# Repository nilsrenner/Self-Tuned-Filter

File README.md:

# Self-Tuned Filter
Backup für die Bachlorarbeit

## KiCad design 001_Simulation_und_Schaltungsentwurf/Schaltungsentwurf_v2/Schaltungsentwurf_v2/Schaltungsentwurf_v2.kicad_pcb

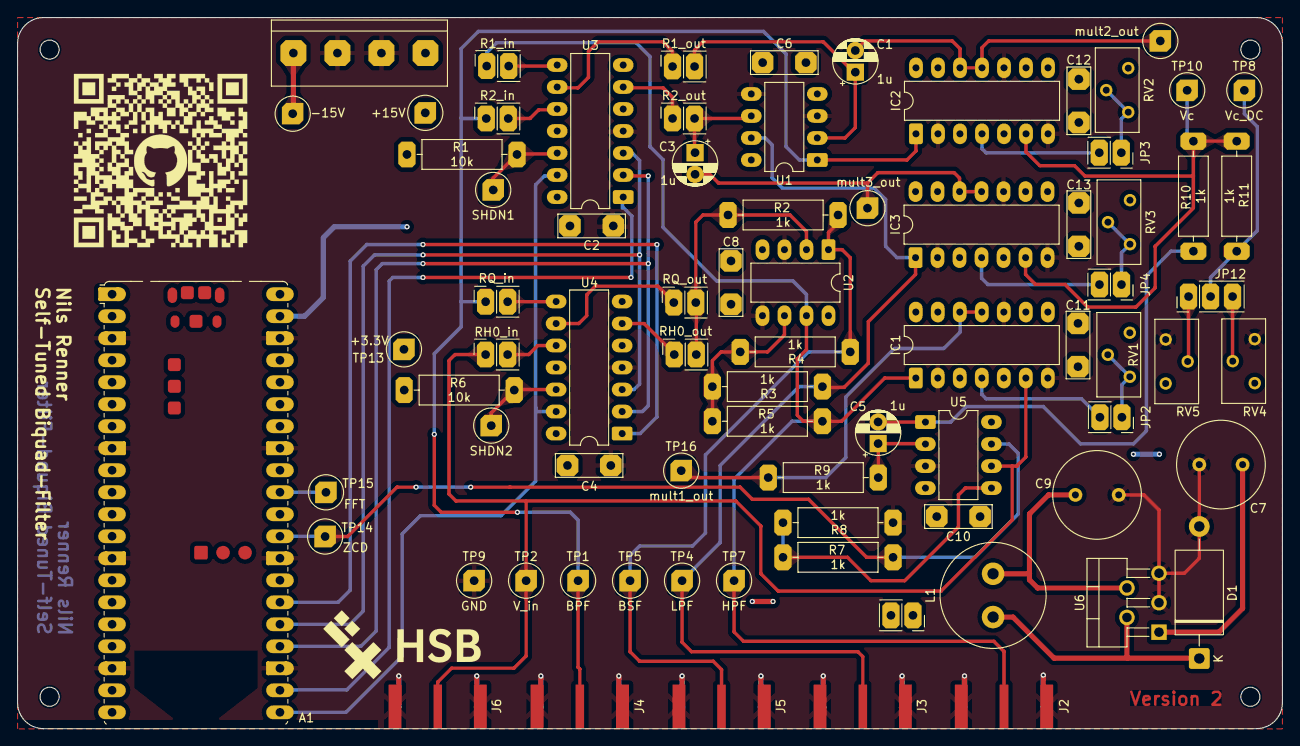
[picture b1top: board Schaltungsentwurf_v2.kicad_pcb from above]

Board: 4 copper layers, 146.0 x 82.1 mm, 84 parts (1 on the bottom side), 48 nets.

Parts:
A1: RaspberryPi_Pico_W; RaspberryPi_Pico_W_THT
C1, C3, C5: 1u; 1-10uF
C2, C4, C6, C8, C10, C11, C12, C13: 100n; 100nF
C7: 470uF; C_Radial_D10.0mm_H16.0mm_P5.00mm
C9: 330uF; C_Radial_D10.0mm_H16.0mm_P5.00mm
D1: 1N5820; D_DO-27_P15.24mm_Horizontal
H1, H2, H3, H4: MountingHole; MountingHole_2.2mm_M2_DIN965
IC1, IC2, IC3: MPY634KP; DIP_14
J1: Screw_Terminal_01x04; Terminal 4 Pol
J2, J3, J4, J5, J6: Conn_Coaxial; BNC Edge Mount
JP1: R1_in; Connector 2 Pin 2.54mm
JP2, JP3, JP4, JP13: Connector 2 Pin 2.54mm
JP5: R1_out; Connector 2 Pin 2.54mm
JP6: R2_in; Connector 2 Pin 2.54mm
JP7: RQ_in; Connector 2 Pin 2.54mm
JP8: RH0_in; Connector 2 Pin 2.54mm
JP9: R2_out; Connector 2 Pin 2.54mm
JP10: RQ_out; Connector 2 Pin 2.54mm
JP11: RH0_out; Connector 2 Pin 2.54mm
JP12: Jumper3; Connector 3 Pin 2,54mm
L1: 68uH; L_Radial_D12.0mm_P5.00mm_Fastron_11P
R1, R6: 10k; Resistor
R2, R3, R4, R5, R7, R8, R9, R10, R11: 1k; Resistor
RV1, RV2, RV3: 10k; Potentiometer_Bourns_3296Y_Vertical
RV4, RV5: 100k; Potentiometer_Bourns_3296Y_Vertical
Ref**: Val**; git_qr
Ref**#2: Val**; logo_nils
TP1: BPF; TestPoint
TP2: V_in; TestPoint
TP3: SHDN1; TestPoint
TP4: LPF; TestPoint
TP5: BSF; TestPoint
TP6: SHDN2; TestPoint
TP7: HPF; TestPoint
TP8: Vc_DC; TestPoint
TP9: GND; TestPoint
TP10: Vc; TestPoint
TP11: +15V; TestPoint
TP12: -15V; TestPoint
TP13: +3.3V; TestPoint
TP14: ZCD; TestPoint
TP15: FFT; TestPoint
TP16: mult1_out; TestPoint
TP17: mult2_out; TestPoint
TP18: mult3_out; TestPoint
U1, U2, U5: TL082; DIP_8
U3, U4: MCP4261-104E_P; DIP_14
U6: LM2596T-3.3; TO-220-5_P3.4x3.7mm_StaggerOdd_Lead3.8mm_Vertical

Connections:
+3.3V: A1.39 (VSYS), C2.1, C4.1, JP13.2 (B), R1.1, R6.1, TP13.1, U3.14 (VDD), U4.14 (VDD)
+15V: C6.1, C7.1, C8.1, C10.1, C11.1, C12.1, C13.1, IC1.14 (+VS), IC2.14 (+VS), IC3.14 (+VS), J1.1, RV4.1, TP11.1, U1.8 (V+), U2.8 (V+), U5.8 (V+), U6.1 (VIN)
-15V: C6.2, C8.2, C10.2, C11.2, C12.2, C13.2, IC1.8 (-VS), IC2.8 (-VS), IC3.8 (-VS), J1.4, RV1.3, RV2.3, RV3.3, RV5.3, TP12.1, U1.4 (V-), U2.4 (V-), U5.4 (V-)
/FFT: A1.31 (GPIO26_ADC0), TP15.1
/ZCD: A1.29 (GPIO22), R7.2, TP14.1, U5.7
BPF: IC2.1 (X_1_INPUT), J4.1 (In), JP6.1 (A), JP7.1 (A), TP1.1, U1.1
BSF: J5.1 (In), R2.2, R4.1, TP5.1, U2.1
CS1: A1.22 (GPIO17), U3.1 (~CS)
CS2: A1.26 (GPIO20), U4.1 (~CS)
GND: A1.3 (GND), A1.8 (GND), A1.13 (GND), A1.18 (GND), A1.23 (GND), A1.28 (GND), A1.33 (AGND), A1.38 (GND), C2.2, C4.2, C7.2, C9.2, D1.2 (A), IC1.2 (X_2_INPUT), IC1.7 (Y_2_INPUT), IC1.10 (Z_2_INPUT), IC2.2 (X_2_INPUT), IC2.7 (Y_2_INPUT), IC2.10 (Z_2_INPUT), IC3.2 (X_2_INPUT), IC3.7 (Y_2_INPUT), IC3.10 (Z_2_INPUT), J1.2, J1.3, J2.2 (Ext), J3.2 (Ext), J4.2 (Ext), J5.2 (Ext), J6.2 (Ext), R8.1, RV4.3, RV5.1, TP9.1, U1.3 (+), U1.5 (+), U2.3 (+), U2.5 (+), U3.4 (VSS), U4.4 (VSS), U5.3 (+), U6.3 (GND), U6.5 (~ON/OFF)
HPF: IC1.1 (X_1_INPUT), J2.1 (In), JP1.1 (A), R5.2, TP7.1, U2.7
LPF: IC3.1 (X_1_INPUT), J3.1 (In), R3.1, TP4.1, U1.7
MISO: A1.21 (GPIO16), U3.13 (SDO), U4.13 (SDO)
MOSI: A1.25 (GPIO19), U3.3 (SDI), U4.3 (SDI)
unnamed: C5.2, R10.1, U5.1
unnamed: D1.1 (K), L1.1, U6.2 (OUT)
unnamed: IC1.4 (SCALE_FACTOR), JP2.2 (B)
unnamed: IC2.4 (SCALE_FACTOR), JP3.2 (B)
unnamed: IC3.4 (SCALE_FACTOR), JP4.2 (B)
unnamed: JP2.1 (A), RV1.1, RV1.2
unnamed: JP3.1 (A), RV2.1, RV2.2
unnamed: JP4.1 (A), RV3.1, RV3.2
unnamed: C1.1, JP5.2 (B), U1.2 (-)
unnamed: C3.1, JP9.2 (B), U1.6 (-)
unnamed: JP10.2 (B), JP11.2 (B), R2.1, U2.2 (-)
unnamed: JP12.1 (A), RV5.2
unnamed: JP12.3 (B), RV4.2
unnamed: JP12.2 (C), R11.2, TP8.1
unnamed: C9.1, JP13.1 (A), L1.2, U6.4 (FB)
unnamed: R3.2, R4.2, R5.1, U2.6 (-)
unnamed: R1.2, TP3.1, U3.12 (~SHDN)
unnamed: R6.2, TP6.1, U4.12 (~SHDN)
unnamed: C5.1, R9.2, U5.2 (-)
unnamed: R7.1, R8.2, U5.5 (+)
R1_in: JP1.2 (B), U3.8 (P0A)
R1_out: JP5.1 (A), U3.9 (P0W)
R2_in: JP6.2 (B), U3.10 (P0B)
R2_out: JP9.1 (A), U3.6 (P1W)
RH0_in: JP8.2 (B), U4.10 (P0B)
RH0_out: JP11.1 (A), U4.6 (P1W)
RQ_in: JP7.2 (B), U4.8 (P0A)
RQ_out: JP10.1 (A), U4.9 (P0W)
SCK: A1.24 (GPIO18), U3.2 (SCK), U4.2 (SCK)
V_in: IC1.6 (Y_1_INPUT), J6.1 (In), JP8.1 (A), TP2.1, U5.6 (-)
Vc: IC2.6 (Y_1_INPUT), IC3.6 (Y_1_INPUT), R10.2, R11.1, TP10.1
mult1_out: IC1.11 (Z_1_INPUT), IC1.12 (OUTPUT), R9.1, TP16.1
mult2_out: C1.2, IC2.11 (Z_1_INPUT), IC2.12 (OUTPUT), TP17.1
mult3_out: C3.2, IC3.11 (Z_1_INPUT), IC3.12 (OUTPUT), TP18.1

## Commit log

2025-09-22 chore: Test von GitHub pages
2025-09-23 Datei gelöscht
2025-10-06 Initializing gh-pages branch
2025-10-06 Built site for gh-pages
2025-10-06 Anpassung für gh-pages
2025-10-06 Ordnerstruktur und Dateien angepasst
2025-10-07 Test für GH Pages (Ordnerumbenennung)
2025-10-09 Weiterarbeit an Sim Plots
2025-10-13 Überarbeitung von SP und Plots
2025-10-15 Weiterarbeit Stand 14.10
2025-10-20 Weiterarbeit Stand 20.10
2025-10-24 Weiterarbeit Stand 24.10 (angepasste Dateigröße)
2025-10-24 Stand 24.10
2025-10-28 Stand 28.10
2025-11-04 Stand 04.11
2025-11-06 Cleaned repo with gitignore and latexmk
2025-11-06 latexmk test, another clean
2025-11-10 Expose und Aux-Datein ge-cleaned
2025-11-10 Lokale Änderungen am KiCad-Projekt gesichert
2025-11-14 Stand 14.11
2025-11-19 Aktueller Stand des Schreibteils hinzugefügt
2025-11-20 Korrekturen
2025-11-20 MIT thesis template
2025-11-25 Erste Iteration des PCBs
2025-11-25 Fix typo in project name from 'Selfe' to 'Self'
2025-12-08 documentation of the PCB (iteration 1)
2025-12-12 Subchapter: Simulation of input signals of different frequencies added
2025-12-16 Improvements to the chapter on sensitivity and Vc
2025-12-18 Fix terminology for center and cutoff frequency
2025-12-29 Improvements on teminology for siunitx
2026-01-05 First version of the SPI bus implementation in MicroPython
2026-01-07 Review Theorie_neu
2026-01-07 Rename and review of 005_self
2026-01-07 ngspice review 005_self-tuned-filter sim
2026-01-07 Einheiten nicht in eckigen Klammern
2026-01-09 Konflikt aufgelöst: Theorie_neu.tex übernommen
2026-01-09 LTspice sim added
2026-01-09 Merge-Konflikt aufgelöst
2026-01-15 Kleine Korrekturen in Theorie_neu
2026-01-19 Alle ungetrackten Dateien hinzugefügt
2026-01-21 Schaden der letzten 10 Tage wieder rückgängig gemacht
2026-01-26 Bestätigung der Gleichung für omega_0
